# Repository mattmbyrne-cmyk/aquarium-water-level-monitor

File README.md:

<meta name="google-site-verification" content="3cnTc2ZwSrkomspXSzRi1tGMBhyJs1C-p10DvXCBGcc" />

# Aquarium Water Level Monitor

## About

An open-source aquarium sump water level monitoring system built around the DFRobot A02YYUW waterproof ultrasonic sensor and an ESP32 microcontroller. The project provides reliable, non-contact water level measurement while keeping all electronics safely away from the water.

The system is specifically designed for aquarium sump installations and includes custom 3D-printable hardware for both the sensor mount and controller enclosure. Real-time water level status is displayed locally using green, yellow, and red LEDs, with an audible alarm to warn when the water level falls below a user-defined threshold.

Through its built-in web interface, users can monitor water levels remotely and configure operating parameters without modifying the source code. This helps aquarium owners detect abnormal sump conditions early and maintain consistent water levels for reliable operation of filtration and top-off systems.

## Features

- Built-in web interface for monitoring and configuration
- User-configurable high and low level alarms with millimeter precision
- Green, yellow, and red LED water level status indicators
- Audible low-water-level alarm
- Optimized for aquarium tank or sump installations
- Non-contact water level measurement
- Waterproof DFRobot A02YYUW ultrasonic sensor
- Fully open-source hardware and software

## Hardware

- ESP32 development board
- DFRobot A02YYUW waterproof ultrasonic sensor
- RGB LEDs for water level status red, yellow, and green
- Piezo buzzer for audible alarms
- Custom Printed Circuit Board (PCB)

## Applications

- Aquarium sump water level monitoring
- Auto top-off (ATO) system monitoring
- Freshwater reservoir monitoring
- Water storage tank level monitoring
- General-purpose non-contact liquid level measurement

## Web Interface

<table align="center">
  <tr>
    <td align="center">
      <br>
      Configuration Page
    </td>
    <td align="center">
      <br>
      Tank Full
    </td>
    <td align="center">
      <br>
      Tank Half Full
    </td>
    <td align="center">
      <br>
      Tank Empty - Buzzer On
    </td>
  </tr>
</table>

## Assembled Project

<table align="center">
  <tr>
    <td align="center">
      <br>
      Front View
    </td>
    <td align="center">
      <br>
      Back View
    </td>
    <td align="center">
      <br>
      Assembled Componets
    </td>
  </tr>
</table>

## Printed Circuit Boad (PCB)

The PCB was designed using KiCad 10.0 Community Edition. All project source files are included in the PCB directory, allowing you to modify and adapt the design to suit your specific requirements.

<table align="center">
  <tr>
    <td align="center">
      <br>
      PCB Top View
    </td>
    <td align="center">
      <br>
      PCB Bottom View
    </td>
    <td align="center">
      <br>
      PCB Layout
    </td>
    <td align="center">
      <br>
      Schematic
    </td>
  </tr>
</table>

## 3D Printed Components

The enclosure and mounting components were printed on a Bambu Lab P1S using Bambu Lab Basic PLA, with Polymaker PolySupport Breakaway Filament employed for the interface layers to improve surface quality and ease support removal. Both the STL files and the original 3MF project files are included in the STL directory, enabling straightforward printing and easy customization of print settings.

<table align="center">
  <tr>
    <td align="center">
      <br>
      Front View
    </td>
    <td align="center">
      <br>
      Back View
    </td>
    <td align="center">
      <br>
      Lid
    </td>
    <td align="center">
      <br>
      Sensor Mount
    </td>
  </tr>
</table>

## OpenSCAD Source Files

The OpenSCAD source files are included in the OpenSCAD directory, allowing you to modify the enclosure or mounting system to suit your specific requirements.

<table align="center">
  <tr>
    <td align="center">
      <br>
      OpenSCAD Front View
    </td>
    <td align="center">
      <br>
      OpenSCAD Back View
    </td>
    <td align="center">
      <br>
      OpenSCAD Mounting
    </td>
   </tr>
</table>

## 🛒 Bill of Materials and Links to Purchase

| Item | Purchase Link |
|---|---|
| ESP32 ESP-WROOM-32 Development Board WiFi + Bluetooth | [Amazon](https://link.amazon/B0espH4Ix) |
| PCB Board - Send the  gerbers files in the PCB folder | JLCPCB or PCBWay |
| Right Angle USB C Flat Extension Cable | [Amazon](https://link.amazon/B0bMhexuD) |
| Waterproof Ultrasonic Ranging Sensor | [Amazon](https://link.amazon/B0bCV0Zxt) |
| LED Light Kit Box - 5 Colors | [Amazon](https://link.amazon/B04djoovX) |
| 220 Ohm Resistor 1/2W (0.5 Watt) | [Amazon](https://link.amazon/B0dC10wjN) |
| DC 3-12V Active Electronic Buzzer | [Amazon](https://link.amazon/B0bWC1ZQ9) |
| JST Connector Kit 2.0mm - 2 and 4 Pin | [Amazon](https://link.amazon/B0aqEWpW9) |
| Self Tapping Screw M2x4 | [Amazon](https://link.amazon/B039ca9Il) |
| Bambu Lab PLA 3D Printer Filament 1.75mm RFID | [Amazon](https://link.amazon/B09fCrKce) |
| Polymaker PolySupport Breakaway Filament | [Amazon](https://link.amazon/B0hEaRlfZ) |

> **Affiliate Disclosure:** Some of the links above are Amazon affiliate links. As an Amazon Associate, I may earn from qualifying purchases at no additional cost to you.

# Quick Start Guide

1. Order the PCB from your preferred manufacturer. The Gerber files included in this repository are production-ready and can be uploaded directly to services such as JLCPCB or PCBWay.

2. Assemble the PCB and install all components, including the ESP32, DFRobot A02YYUW ultrasonic sensor, LEDs, and buzzer.

3. Upload the firmware to the ESP32 using the Arduino IDE via the USB-C port, or using the Web Flash link at the bottom of this page.

4. Power on the device. Using your phone, tablet, or computer, connect to the Wi-Fi hotspot named **Watersensor2.local**.

5. The captive portal should open automatically. If it does not, open a web browser and navigate to:

   http://Watersensor2.local

6. Enter your home Wi-Fi SSID and password.

7. Configure the water level thresholds in millimetres. The default settings are:
   - Low Water Level: 40 mm
   - High Water Level: 140 mm

8. Click **Save**. The device will reboot and automatically connect to your home Wi-Fi network.

9. Once connected, the web interface can be accessed at any time from any device on your network by visiting:

   http://Watersensor2.local

## Web Flash Tool

For users who are not familiar with the Arduino IDE or compiling firmware, a Web Flash Tool is included. This allows you to quickly install the firmware onto your ESP32 development board directly from your web browser. Simply connect the ESP32 to your computer using a USB-C cable and follow the prompts to flash the firmware.

https://mattmbyrne-cmyk.github.io/aquarium-water-level-monitor/

## You're Ready!

The Aquarium Water Level Monitor is now configured and actively monitoring your sump water level. Visual and audible alerts will be triggered whenever the water level falls below your configured minimum threshold, helping you detect evaporation, pump failures, and other water level issues before they become critical.

## Support - Buy Me a Coffee Please

If my work has saved you time, taught you something new, or inspired your own project, consider buying me a coffee. Your support directly helps fund future development and new projects.

☕ Buy Me a Coffee: https://buymeacoffee.com/mattmbyrne

Every contribution helps fund prototyping, PCB manufacturing, testing, and documentation.

## Troubleshooting Tips
In Arduino IDE, if you are using the same board as I listed in the hardware section, select Board Type ESP32 Dev Module
If the Captive Portal doesn't display on iPhones, in the WiFi Properties, disable Limit IP Tracking 

## License
This project is licensed under the MIT License - see the LICENSE file for details.

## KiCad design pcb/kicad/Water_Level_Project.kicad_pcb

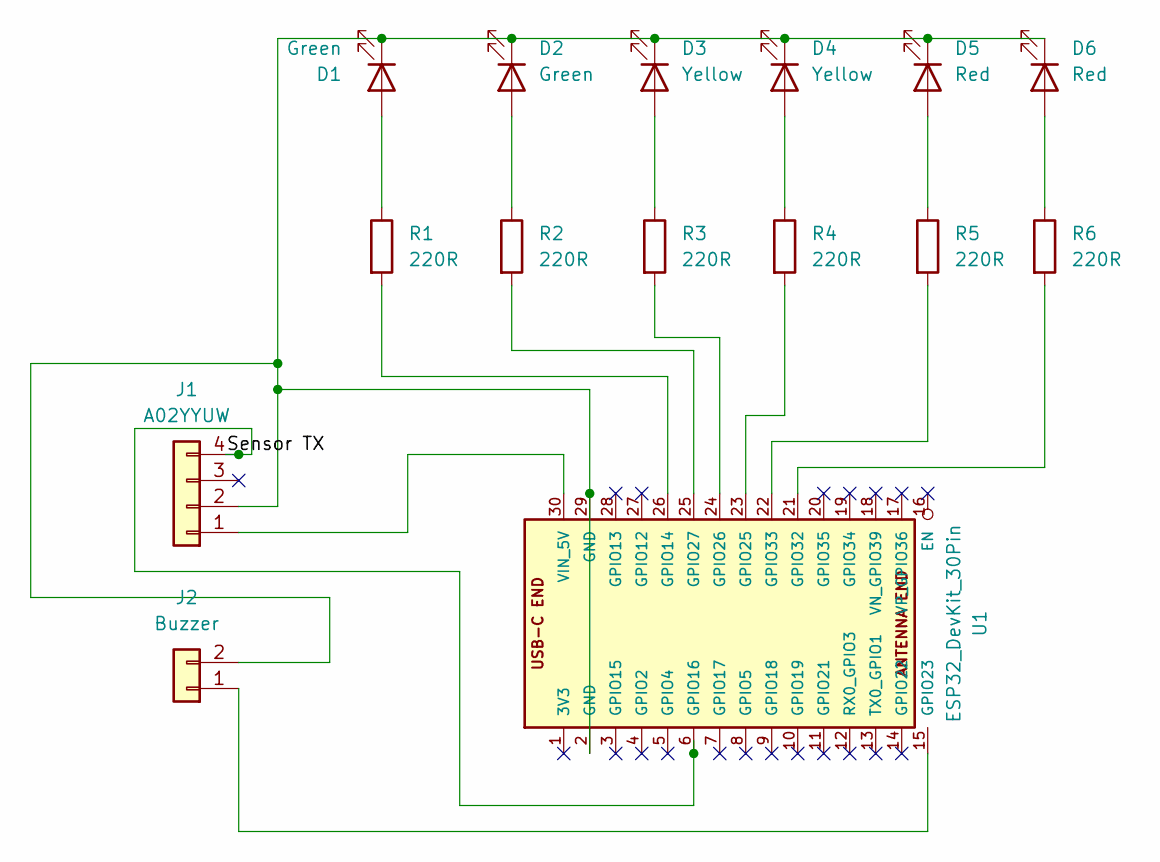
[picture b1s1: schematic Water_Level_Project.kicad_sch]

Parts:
D1, D2: Green; LED_D5.0mm
D3, D4: Yellow; LED_D5.0mm
D5, D6: Red; LED_D5.0mm
J1: A02YYUW; PinHeader_1x04_P2.54mm_Vertical
J2: Buzzer; PinHeader_1x02_P2.54mm_Vertical
R1, R2, R3, R4, R5, R6: 220R; R_Axial_DIN0207_L6.3mm_D2.5mm_P10.16mm_Horizontal
U1: ESP32_DevKit_30Pin; ESP32_DevKit_30Pin_25.2mm

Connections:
/Sensor TX: J1.4, U1.6 (GPIO16)
unnamed: D1.2 (A), R1.1
unnamed: D1.1 (K), D2.1 (K), D3.1 (K), D4.1 (K), D5.1 (K), D6.1 (K), J1.2, J2.2, U1.2 (GND), U1.29 (GND)
unnamed: D2.2 (A), R2.1
unnamed: D3.2 (A), R3.1
unnamed: D4.2 (A), R4.1
unnamed: D5.2 (A), R5.1
unnamed: D6.2 (A), R6.1
unnamed: J1.1, U1.30 (VIN_5V)
unnamed: J2.1, U1.15 (GPIO23)
unnamed: R1.2, U1.26 (GPIO14)
unnamed: R4.2, U1.23 (GPIO25)
unnamed: R3.2, U1.24 (GPIO26)
unnamed: R2.2, U1.25 (GPIO27)
unnamed: R6.2, U1.21 (GPIO32)
unnamed: R5.2, U1.22 (GPIO33)

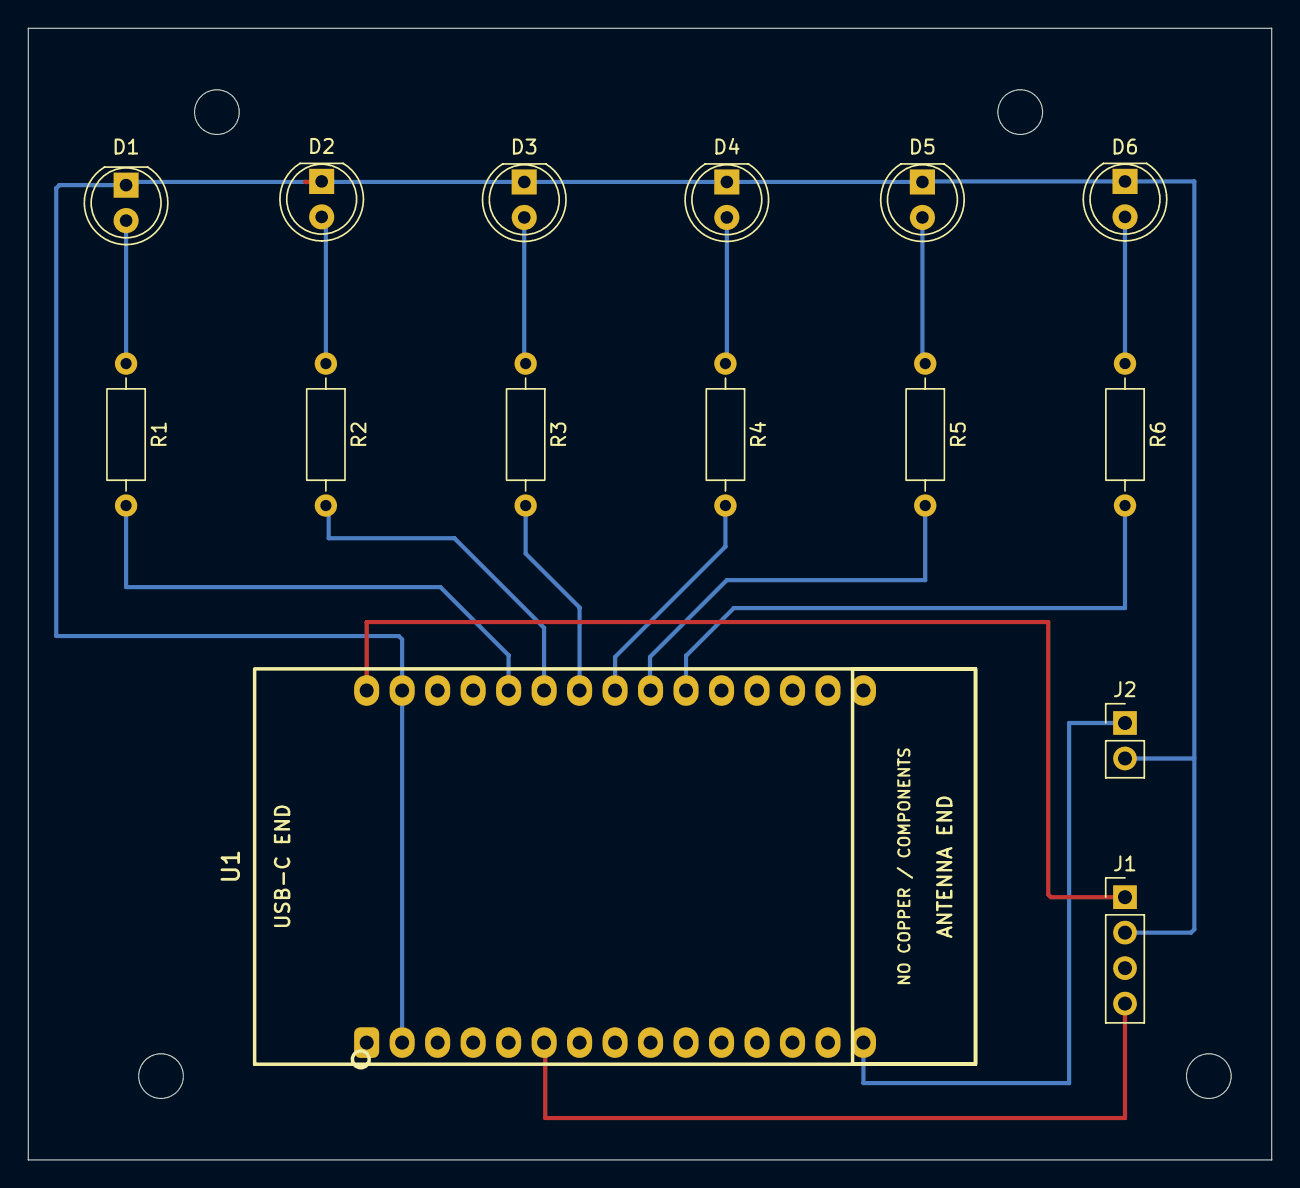
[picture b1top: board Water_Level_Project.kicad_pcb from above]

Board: 2 copper layers, 89.0 x 81.0 mm, 15 parts (0 on the bottom side), 16 nets.

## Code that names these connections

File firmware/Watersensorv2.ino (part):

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  -------------
  A02YYUW VCC -> ESP32 5V/VIN
  A02YYUW GND -> ESP32 GND
  A02YYUW TX  -> ESP32 GPIO16
  A02YYUW RX  -> Not connected

   OUTPUT WIRING (Left to Right)
  -------------
  Red LED 1    -> GPIO14 through 220-ohm resistor
  Red LED 2    -> GPIO27 through 220-ohm resistor
  Yellow LED 1 -> GPIO26 through 220-ohm resistor
  Yellow LED 2 -> GPIO25 through 220-ohm resistor
  Green LED 1  -> GPIO33 through 220-ohm resistor
  Green LED 2  -> GPIO32 through 220-ohm resistor


  Active buzzer positive -> GPIO23
  Active buzzer negative -> GND

  WATER LEVEL INDICATION
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
      Serial.println(
          "ERROR: No valid sensor data. "
          "Check VCC, GND, and sensor TX -> GPIO16."
      );
    }
  }
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

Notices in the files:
firmware/Watersensorv2.ino:
Copyright (c) 2026 Matthew Byrne (mattmbyrne-cmyk)
See LICENSE file in the project root for full license information.
